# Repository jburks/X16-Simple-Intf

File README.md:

# X16-Simple-Intf

This is a proof of concept interface between the X16's 6502 bus and a modern microcontroller. This could be done much more simply with a CPLD, but in keeping with the "retro feel" of the X16, this was implement using all 74xx logic in a DIP package. 

Note: The X16 card edge in the design may be mirrored. Until this can be validated, use at your own risk!

## Host Software Operation

This interface contains two exposed memory addresses and three functional registers:

| Address | Name | Description |
| ------- | ---- | -------- |
| 0 | HOST_WR | Data byte from host to client, write only |
| 0 | HOST_RD | Data byte from client, read only |
| 1 | STATUS | Status flags for card and client, read only |

As can be seen from above, address 0 is used for both the read and write registers. The card only looks at the A0 address line which results in the HOST_XX registers appearing at all even addresses within the selected IO region and the STATUS register at all odd addresses.

The flags of the STATUS register are

| Bit | Name | Description |
| --- | ---- | ----------- |
| 0 | CSTAT_0 | Client status 0. This value reflects the state of the STAT_0 input pin from the client. Interpretation of the meaning of this flag is implementation dependent. |
| 1 | CSTAT_1 | Client status 1. This value reflects the state of the STAT_1 input pin from the client. Interpretation of the meaning of this flag is implementation dependent. |
| 2-5 | UNUSED | Unused status bits. Will contain the same values as the HOST_RD register. |
| 6 | BUSY | Client busy status. This bit indicates that the client has not yet acknowledged the last byte transmitted from the host. |
| 7 | ATTN | Attention. Indicates that the client is trying to get the host's attention. If jumper J2 on the card is closed, the /IRQ line will be held low (asserted) while ATTN is asserted. |

The position of the BUSY and ATTN flags is intended to allow the host software to determine their state via the `BIT` instruction.

## Microcontroller Interface Operation

The design exposes a total of 21 IO signals to a microcontroller. The direction below is specified relative to the card. "I" (Input) indicates a signal from the microcontroller to the card and "O" (Output) indicates a signal from the card to the microcontroller.

The IO signals are

| Pin | Function | Direction | Notes |
| -------- | ----------- | --- | --- |
| H_D0 - H_D7 | Host data | O | The last byte of data sent from the host. This byte is stored in a register and does not reflect the state of the 6502 data bus. |
| C_D0 - C_D7 | Client data | I | A byte of data sent from the microcontroller to the host.This byte is not stored in a register and should be maintained by the microcontroller until it is no longer needed (as determined by the implementation). |
| ATTN | Client attention | I | Should be set high by the microcontroller to indicate that it wants the host's attention. The pin state should be maintained by the microcontroller until host attention is no longer needed. |
| BUSY | Host attention | O | Indicates that the host has written a byte to the HOST_WR register that the microcontroller has not acknowledged. The card is reporting to the host that the microcontroller is busy. |
| ACK | Acknowledge | I | A strobe on this pin by the microcontroller will clear the BUSY signal. This pin should not be held high, asserting it for ~10ns is sufficient. |
| STAT_0 - STAT_1 | Status 0/1 | I | Implementation-dependent status signals. The state of these inputs can be read by the host in the CSTAT_0 and CSTAT_1 flags of the STATUS register. |

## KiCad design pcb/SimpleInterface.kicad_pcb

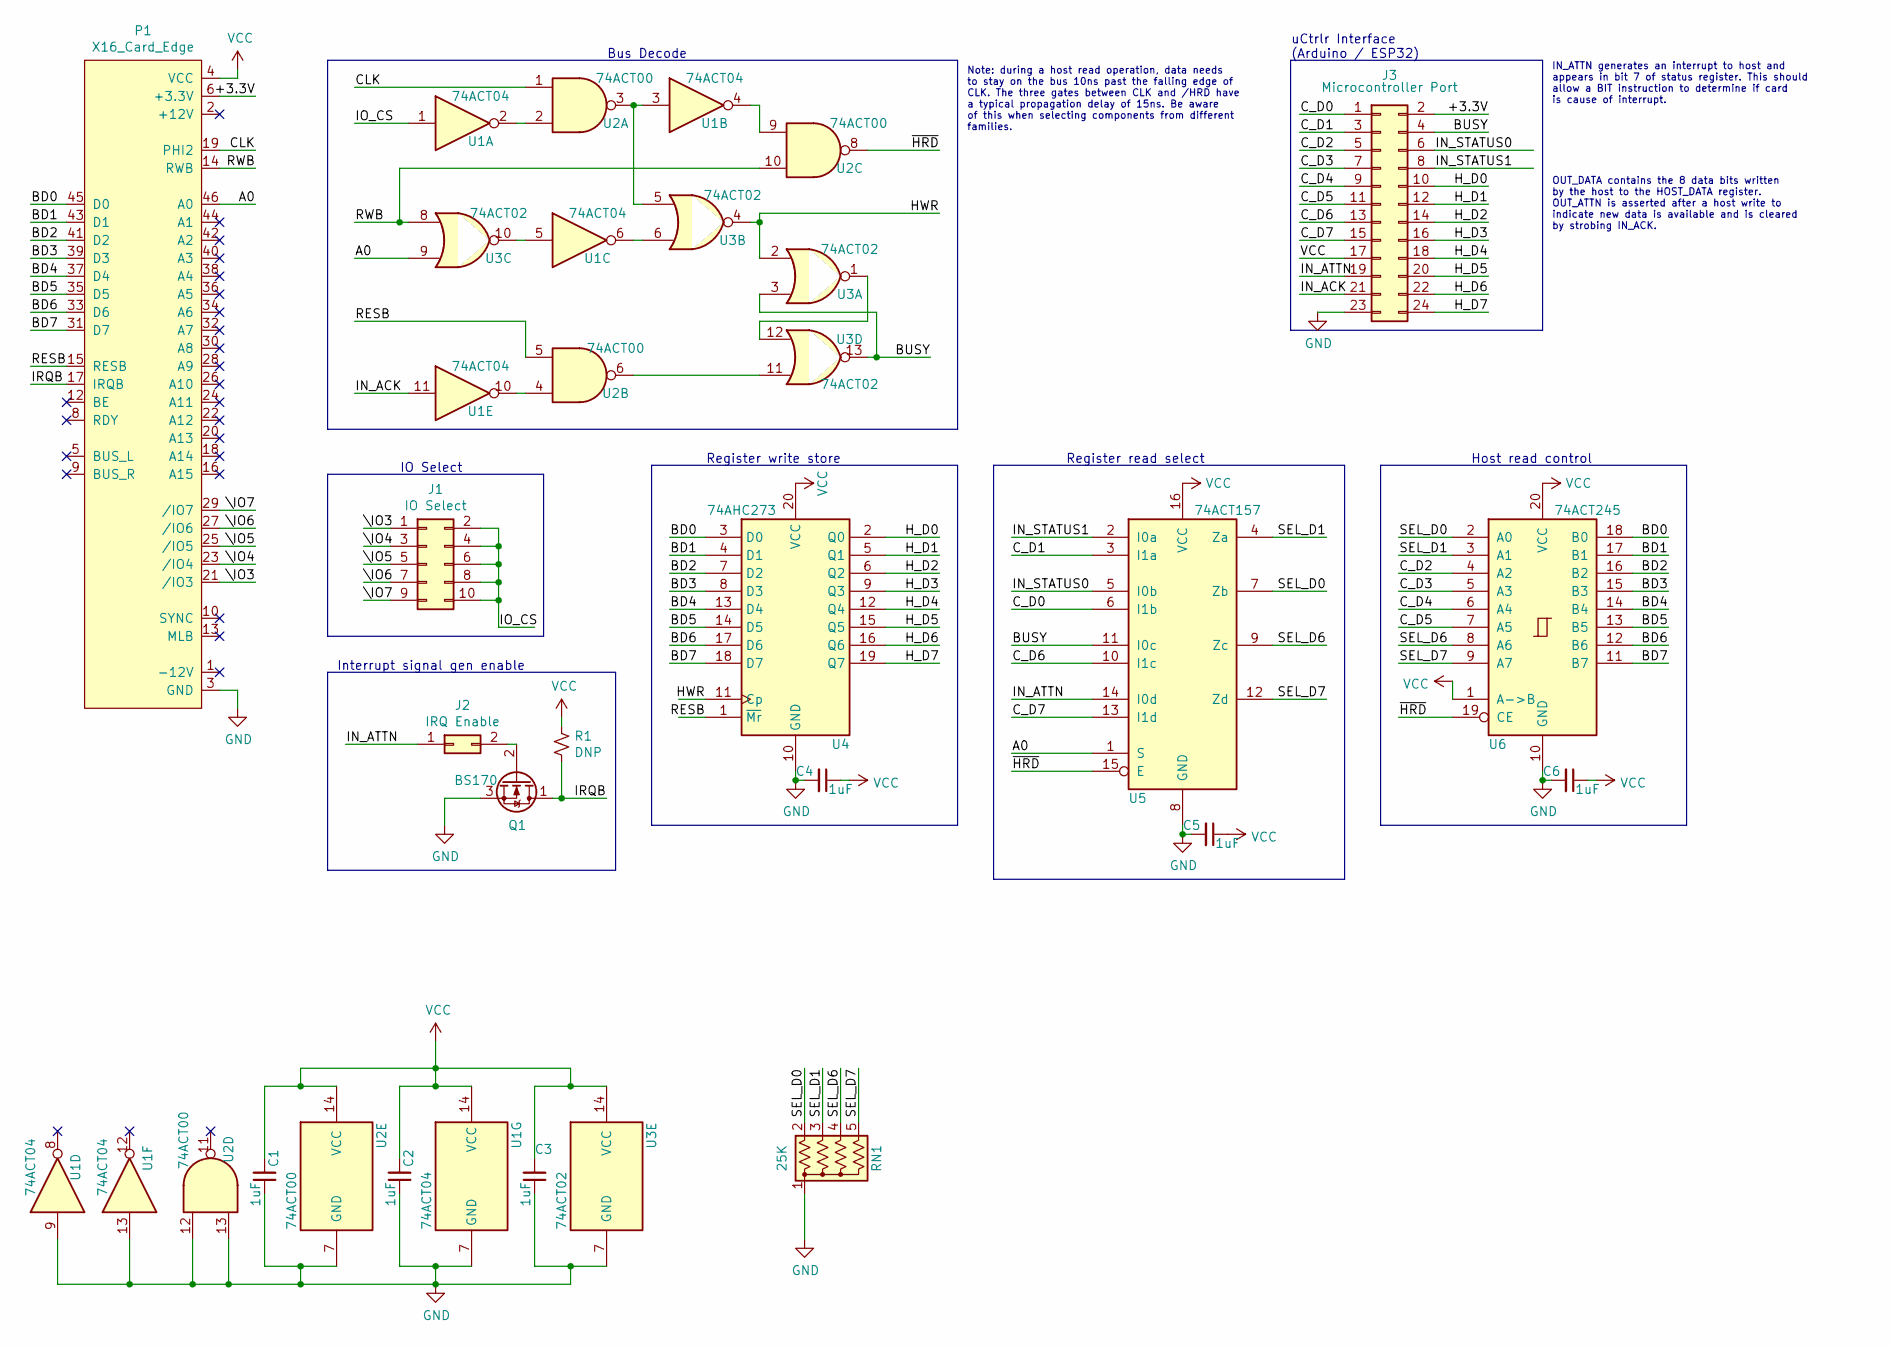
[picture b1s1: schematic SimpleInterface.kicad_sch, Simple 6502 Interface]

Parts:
C1, C2, C3, C4, C5, C6: 1uF; C_Disc_D4.3mm_W1.9mm_P5.00mm
J1: IO Select; PinHeader_2x05_P2.54mm_Vertical
J2: IRQ Enable; PinHeader_2x01_P2.54mm_Vertical
J3: Microcontroller Port; PinHeader_2x12_P2.54mm_Vertical
P1: X16_Card_Edge
Q1: BS170; TO-92_Inline
R1: DNP; R_Axial_DIN0309_L9.0mm_D3.2mm_P12.70mm_Horizontal
RN1: 25K; R_Array_SIP5
U1: 74ACT04; DIP-14_W7.62mm
U2: 74ACT00; DIP-14_W7.62mm
U3: 74ACT02; DIP-14_W7.62mm
U4: 74AHC273; DIP-20_W7.62mm
U5: 74ACT157; DIP-16_W7.62mm
U6: 74ACT245; DIP-20_W7.62mm

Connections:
/+3.3V: J3.2, P1.6 (+3.3V)
/A0: P1.46 (A0), U3.9, U5.1 (S)
/BD0: P1.45 (D0), U4.3 (D0), U6.18 (B0)
/BD1: P1.43 (D1), U4.4 (D1), U6.17 (B1)
/BD2: P1.41 (D2), U4.7 (D2), U6.16 (B2)
/BD3: P1.39 (D3), U4.8 (D3), U6.15 (B3)
/BD4: P1.37 (D4), U4.13 (D4), U6.14 (B4)
/BD5: P1.35 (D5), U4.14 (D5), U6.13 (B5)
/BD6: P1.33 (D6), U4.17 (D6), U6.12 (B6)
/BD7: P1.31 (D7), U4.18 (D7), U6.11 (B7)
/BUSY: J3.4, U3.3, U3.13, U5.11 (I0c)
/CLK: P1.19 (PHI2), U2.1
/C_D0: J3.1, U5.6 (I1b)
/C_D1: J3.3, U5.3 (I1a)
/C_D2: J3.5, U6.4 (A2)
/C_D3: J3.7, U6.5 (A3)
/C_D4: J3.9, U6.6 (A4)
/C_D5: J3.11, U6.7 (A5)
/C_D6: J3.13, U5.10 (I1c)
/C_D7: J3.15, U5.13 (I1d)
/HWR: U3.2, U3.4, U4.11 (Cp)
/H_D0: J3.10, U4.2 (Q0)
/H_D1: J3.12, U4.5 (Q1)
/H_D2: J3.14, U4.6 (Q2)
/H_D3: J3.16, U4.9 (Q3)
/H_D4: J3.18, U4.12 (Q4)
/H_D5: J3.20, U4.15 (Q5)
/H_D6: J3.22, U4.16 (Q6)
/H_D7: J3.24, U4.19 (Q7)
/IN_ACK: J3.21, U1.11
/IN_ATTN: J2.1, J3.19, U5.14 (I0d)
/IN_STATUS0: J3.6, U5.5 (I0b)
/IN_STATUS1: J3.8, U5.2 (I0a)
/IO_CS: J1.2, J1.4, J1.6, J1.8, J1.10, U1.1
/IRQB: P1.17 (IRQB), Q1.1 (D), R1.2
/RESB: P1.15 (RESB), U2.5, U4.1 (~Mr)
/RWB: P1.14 (RWB), U2.10, U3.8
/SEL_D0: RN1.2 (R1), U5.7 (Zb), U6.2 (A0)
/SEL_D1: RN1.3 (R2), U5.4 (Za), U6.3 (A1)
/SEL_D6: RN1.4 (R3), U5.9 (Zc), U6.8 (A6)
/SEL_D7: RN1.5 (R4), U5.12 (Zd), U6.9 (A7)
/\IO3: J1.1, P1.21 (/IO3)
/\IO4: J1.3, P1.23 (/IO4)
/\IO5: J1.5, P1.25 (/IO5)
/\IO6: J1.7, P1.27 (/IO6)
/\IO7: J1.9, P1.29 (/IO7)
/~HRD: U2.8, U5.15 (E), U6.19 (CE)
GND: C1.1, C2.1, C3.1, C4.2, C5.2, C6.2, J3.23, P1.3 (GND), P1.7 (GND), P1.11 (GND), P1.48 (GND), Q1.3 (S), RN1.1 (common), U1.7 (GND), U1.9, U1.13, U2.7 (GND), U2.12, U2.13, U3.7 (GND), U4.10 (GND), U5.8 (GND), U6.10 (GND)
unnamed: J2.2, Q1.2 (G)
unnamed: U1.2, U2.2
unnamed: U1.3, U2.3, U3.5
unnamed: U1.4, U2.9
unnamed: U1.5, U3.10
unnamed: U1.6, U3.6
unnamed: U1.10, U2.4
unnamed: U2.6, U3.11
unnamed: U3.1, U3.12
VCC: C1.2, C2.2, C3.2, C4.1, C5.1, C6.1, J3.17, P1.4 (VCC), P1.47 (VCC), R1.1, U1.14 (VCC), U2.14 (VCC), U3.14 (VCC), U4.20 (VCC), U5.16 (VCC), U6.1 (A->B), U6.20 (VCC)

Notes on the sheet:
OUT_DATA contains the 8 data bits written by the host to the HOST_DATA register. OUT_ATTN is asserted after a host write to indicate new data is available and is cleared by strobing IN_ACK.
Register write store
Note: during a host read operation, data needs to stay on the bus 10ns past the falling edge of CLK. The three gates between CLK and /HRD have a typical propagation delay of 15ns. Be aware of this when selecting components from different families.
Interrupt signal gen enable
uCtrlr Interface (Arduino / ESP32)
IN_ATTN generates an interrupt to host and appears in bit 7 of status register. This should allow a BIT instruction to determine if card is cause of interrupt.
Bus Decode
Host read control
IO Select
Register read select

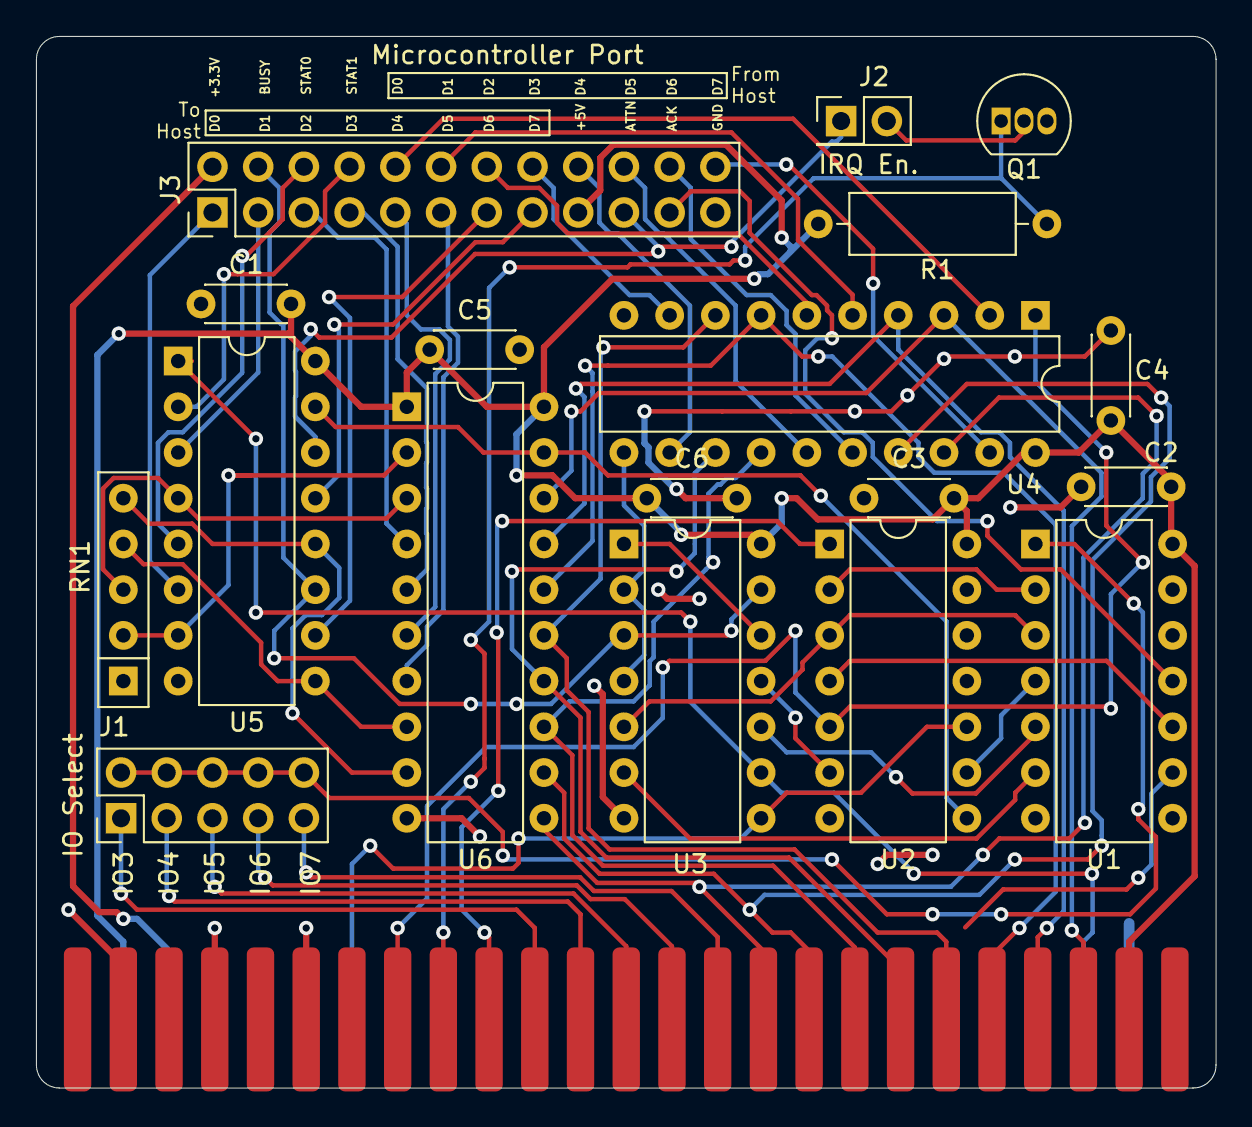
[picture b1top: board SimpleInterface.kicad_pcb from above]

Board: 2 copper layers, 65.5 x 58.4 mm, 19 parts (0 on the bottom side), 58 nets.

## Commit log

2022-03-16 Fixed 3D board rendering and added PNG of 3D rendered board; add KiCAD 6 schematic file.
2022-03-16 Ambiguous data bus renaming: Bus signals named "CDn" for Client, "HDn" for Host, and "BDn" for Bus.
